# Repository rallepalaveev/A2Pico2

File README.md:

# A2Pico2

This space is decicated to A2Pico2 Project.

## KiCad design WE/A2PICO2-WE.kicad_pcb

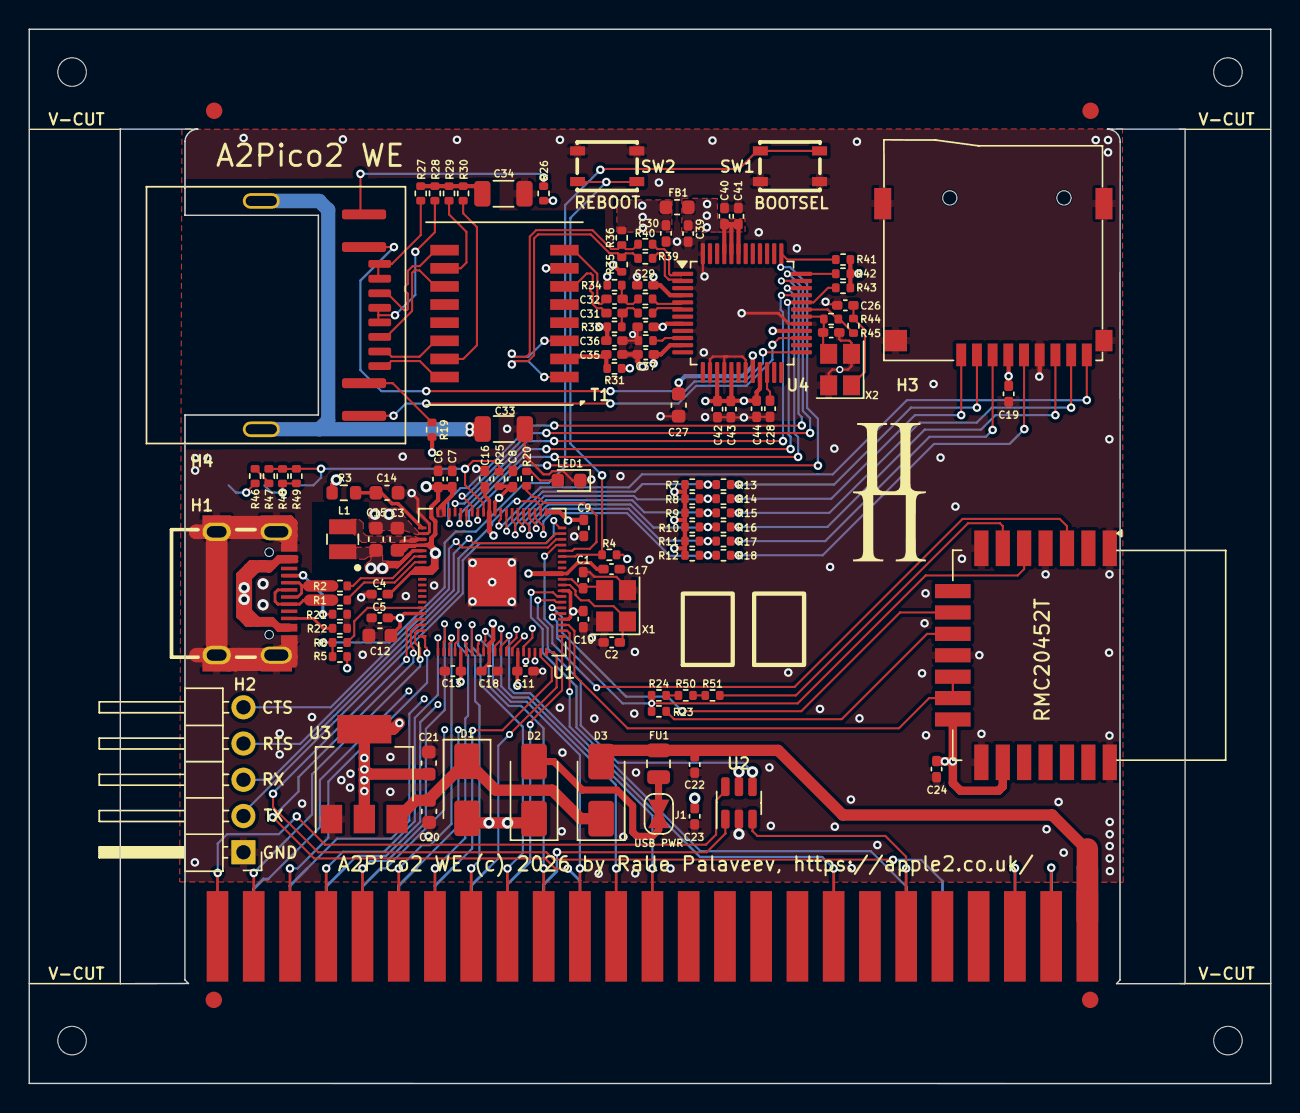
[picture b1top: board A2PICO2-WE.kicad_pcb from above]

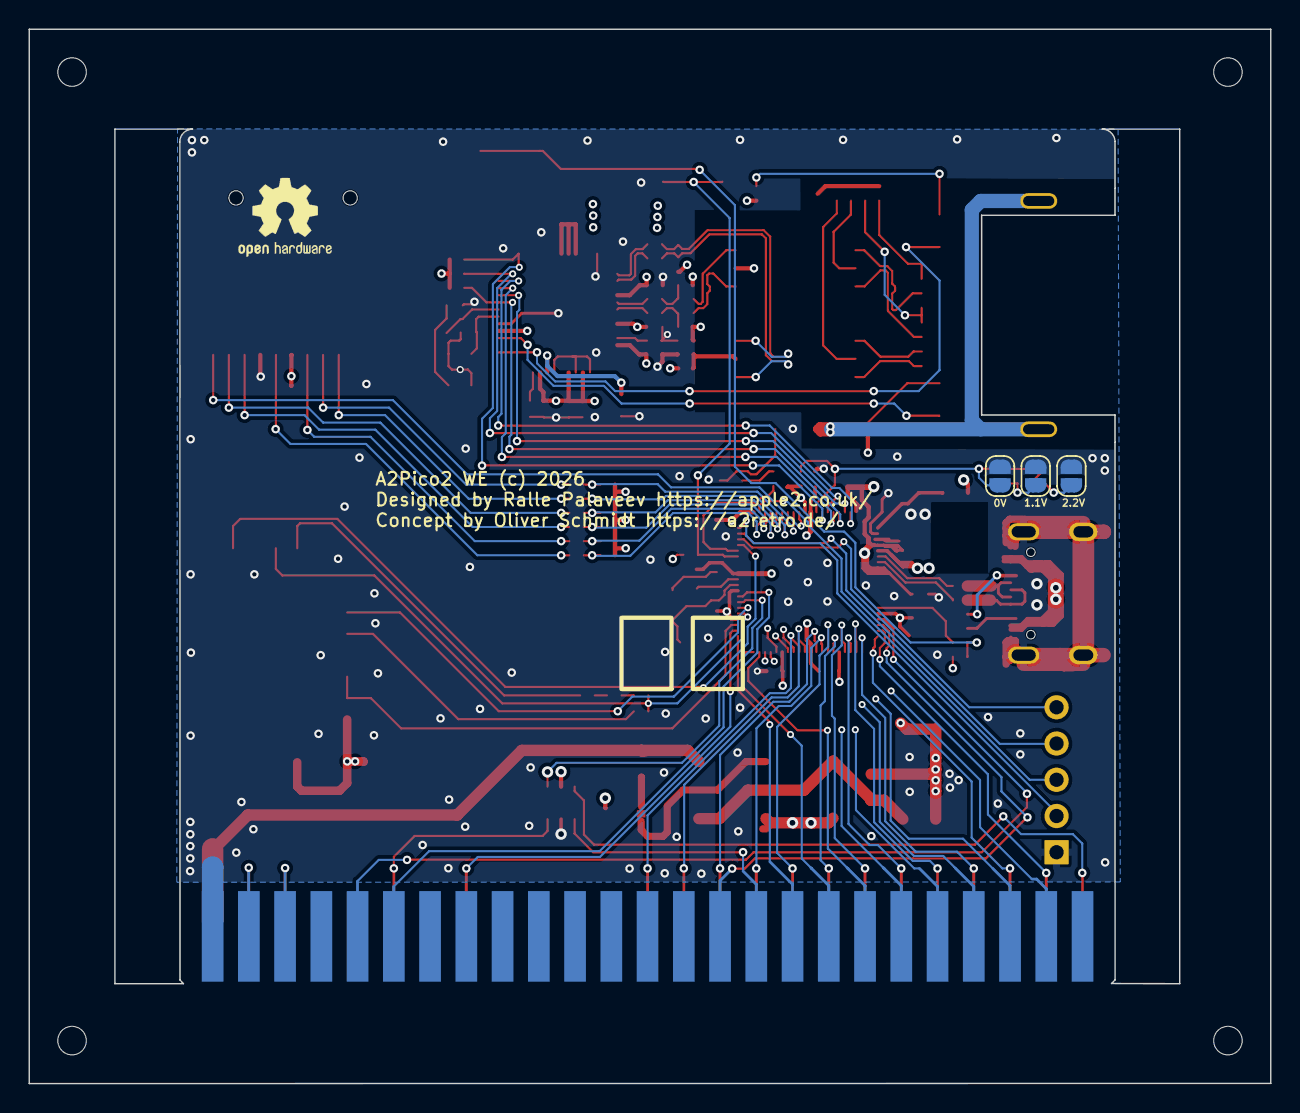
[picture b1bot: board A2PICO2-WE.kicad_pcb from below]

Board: 4 copper layers, 87.0 x 73.9 mm, 120 parts (3 on the bottom side), 90 nets.

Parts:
C1, C2, C25, C26: 18pF; C_0402_1005Metric_Pad0.74x0.62mm_HandSolder
C3, C12, C14, C27: 4.7uF; C_0603_1608Metric
C4, C5, C6, C7, C8, C9, C10, C11, C13, C16, C17, C18, C19, C22, C23, C24, C36, C37, C38, C39, C40, C41, C42, C43, C44: 100n; C_0402_1005Metric_Pad0.74x0.62mm_HandSolder
C15, C20, C21: 10uF; C_0603_1608Metric
C28: 10n; C_0402_1005Metric_Pad0.74x0.62mm_HandSolder
C29: 1u; C_0402_1005Metric_Pad0.74x0.62mm_HandSolder
C30: 1uF; C_0402_1005Metric_Pad0.74x0.62mm_HandSolder
C31, C32: 6.8n; C_0402_1005Metric_Pad0.74x0.62mm_HandSolder
C33, C34: 1nF/2kV; C_1206_3216Metric
C35: 22n; C_0402_1005Metric_Pad0.74x0.62mm_HandSolder
D1, D2, D3: SS14; D_SMA
FB1: 600Ω@100 MHz; L_0603_1608Metric
FU1: 500mA; Fuse_0805_2012Metric
H1: USB-C-16P-F(A40-00119-A52-12); USB2.0_TYPE-C(A40-00119-A52-12)
H2: PinHeader_1x05_P2.54mm_Horizontal
H3: microSD_Shou_Han; microSD_HC_Hirose_DM3AT-SF-PEJM5
H4: RJ45; RJ45_Pulse_JXD6-0001NL_Horizontal
J1: SolderJumper-2_P1.3mm_Bridged_RoundedPad1.0x1.5mm
J2, J3, J4: SolderJumper-2_P1.3mm_Open_RoundedPad1.0x1.5mm
L1: 3.3uH; L_Wuerth_MAPI-2512
LED1: LED_CHR; LED_0603_1608Metric
R1, R2: 27; R_0402_1005Metric
R3: 27; R_0603_1608Metric
R4, R6, R25, R46, R47, R48, R49: 1k; R_0402_1005Metric
R5, R7, R8, R9, R10, R11, R12, R23: 10k; R_0402_1005Metric
R13, R14, R15, R16, R17, R18, R33, R34, R35, R36: 49.9; R_0402_1005Metric
R19, R24, R26: 330; R_0402_1005Metric
R20: 1K; R_0402_1005Metric
R21, R22: 5k1; R_0402_1005Metric
R27, R28, R29, R30, R50, R51: 75; R_0402_1005Metric
R31: 10/1%; R_0402_1005Metric
R32: 12.4k/1%; R_0402_1005Metric
R37, R38, R39, R40: 3.3; R_0402_1005Metric
R41, R42, R43: 5.1k; R_0402_1005Metric
R44: 1M; R_0402_1005Metric
R45: 0; R_0402_1005Metric
RMC20452T: RMC20452T; ESP-12E
SW1, SW2: YTS-A016-X
T1: TDFN-12_2x3mm_P0.5mm
U1: RP2354B; QFN-80_EP_10x10_Pitch0.4mm
U2: SN74LVC1G11DBVR; SOT-23-6
U3: AZ1117I-H-3.3; SOT-223-3_TabPin2
U4: LQFP-48_7x7mm_P0.5mm
X1, X2: Crystal_SMD_Abracon_ABM8AIG-4Pin_3.2x2.5mm

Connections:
1V2O: C28.2, U4.22
45: H4.4, H4.5, R28.1
75: C34.1, R27.2, R28.2, R29.2, R30.2
78: H4.7, H4.8, R27.1
+1.1V: C15.1, C16.1, C17.1, C18.1, L1.1, U1.10 (DVDD), U1.32 (DVDD), U1.51 (DVDD), U1.65 (VREG_FB)
+3V3: C3.1, C4.1, C5.1, C6.1, C7.1, C8.1, C9.1, C10.1, C11.1, C12.1, C13.1, C19.1, C21.2, C23.1, C24.2, C39.2, C40.1, C41.1, FB1.1, H3.4, R3.2, R4.1, R5.2, R7.1, R8.1, R9.1, R10.1, R11.1, R12.1, R19.1, R25.1, R26.1, R41.2, R42.2, R43.2, RMC20452T.14, RMC20452T.16, U1.5 (IOVDD), U1.15 (IOVDD), U1.24 (IOVDD), U1.29 (IOVDD), U1.41 (IOVDD), U1.50 (IOVDD), U1.59 (IOVDD), U1.60 (IOVDD), U1.64 (VREG_VIN), U1.68 (IOVDD), U1.69 (IOVDD), U1.76 (IOVDD), U2.5, U3.2, U4.28, U4.43, U4.44, U4.45
+3V3a: C29.2, C30.2, C37.2, C38.2, C42.2, C43.2, C44.2, FB1.2, R31.2, R35.1, R36.2, U4.4, U4.8, U4.11, U4.15, U4.17, U4.21
+5V: C22.2, D3.2, FU1.1
+5V-1: D2.2, FU1.2, J1.1, J1.2
/BOOTSEL: R5.1, R6.1, SW1.1
/D+: R1.2, U1.67 (USB_D+)
/D-: R2.2, U1.66 (USB_D-)
/USB_D+: H1.A6, H1.B6, R1.1
/USB_D-: H1.A7, H1.B7, R2.1
/VIN: C20.1, D1.1, D3.1, U3.3
/~QSPI_CS_{0}: R6.2, U1.75 (~QSPI_CS)
A5-net: H1.A5, R21.1
ACTn: H4.11, U4.25
ACTn+: H4.12, R26.2
B5-net: H1.B5, R22.1
CLK: R12.2, R18.1, U1.43 (GPIO34)
CLK_: H3.5, R18.2
CMD: R11.2, R17.1, U1.44 (GPIO35)
CMD_: H3.3, R17.2
DAT0: R10.2, R16.1, U1.45 (GPIO36)
DAT0_: H3.7, R16.2
DAT1: R9.2, R15.1, U1.46 (GPIO37)
DAT1_: H3.8, R15.2
DAT2: R8.2, R14.1, U1.47 (GPIO38)
DAT2_: H3.1, R14.2
DAT3: R7.2, R13.1, U1.48 (GPIO39)
DAT3_: H3.2, R13.2
Detect: H3.9, U1.49 (GPIO40)
ETH_CSn: R43.1, U1.56 (GPIO45), U4.32
ETH_INTn: R42.1, U1.54 (GPIO43), U4.36
ETH_RSTn: R41.1, U1.53 (GPIO42), U4.37
ETH_Rx: U1.55 (GPIO44), U4.34
ETH_SCK: U1.57 (GPIO46), U4.33
ETH_Tx: U1.58 (GPIO47), U4.35
ExtCap: C27.2, U4.20
ExtRes: R32.2, U4.10
GND: C1.2, C2.2, C3.2, C4.2, C5.2, C6.2, C7.2, C8.2, C9.2, C10.2, C11.2, C12.2, C13.2, C14.1, C15.2, C16.2, C17.2, C18.2, C19.2, C20.2, C21.1, C22.1, C23.2, C24.1, C25.2, C26.1, C27.1, C28.1, C29.1, C30.1, C33.2, C34.2, C35.2, C36.2, C37.1, C38.1, C39.1, C40.2, C41.2, C42.1, C43.1, C44.1, H1.0, H1.A1, H1.A12, H1.B1, H1.B12, H2.1, H3.6, H3.10, J2.2, J3.2, J4.2, LED1.1 (K), R21.2, R22.2, R32.1, RMC20452T.1, RMC20452T.4, RMC20452T.7, RMC20452T.11, RMC20452T.15, RMC20452T.21, SW1.2, SW2.1, U1.62 (GND), U1.81 (GND), U2.2, U3.1, U4.3, U4.9, U4.14, U4.16, U4.19, U4.29, U4.48, X1.2, X1.4, X2.2, X2.4
HWSel: J4.1, R25.2, R47.1, R48.1, R49.1, U1.52 (GPIO41)
HWSel1.1: J3.1, R48.2, R49.2
HWSel2.2: J2.1, R46.2
HWSel3.3: R46.1, R47.2
LED: R20.1, U1.36 (GPIO28)
LINKn: H4.9, U4.27
LINKn+: H4.10, R19.2
unnamed: C14.2, R3.1, U1.61 (VREG_AVDD)
unnamed: L1.2, U1.63 (VREG_XL)
unnamed: C2.1, U1.30 (XIN), X1.1
unnamed: C1.1, U1.31 (XOUT), X1.3
RCT: C36.1, R33.1, R34.1, T1.7
RD+: C31.1, T1.6
RD-: C32.1, T1.8
RX+: H4.3, T1.11
RX-: H4.6, T1.9
RXCT: R29.1, T1.10
RXN: R38.2, U4.5
RXN_: C32.2, R34.2, R38.1
RXP: R37.2, U4.6
RXP_: C31.2, R33.2, R37.1
TCT: C35.1, R31.1, T1.2
TD+: R35.2, R39.1, T1.1
TD-: R36.1, R40.1, T1.3
TX+: H4.1, T1.16
TX-: H4.2, T1.14
TXCT: R30.1, T1.15
TXN: R40.2, U4.1
TXP: R39.2, U4.2
UART_CTS: H2.5, U1.38 (GPIO30)
UART_RTS: H2.4, U1.39 (GPIO31)
UART_Rx: H2.3, U1.42 (GPIO33)
UART_Tx: H2.2, U1.40 (GPIO32)
VBUS: D1.2, D2.1, H1.A4, H1.A9, H1.B4, H1.B9
WL_CLK: RMC20452T.3, U1.37 (GPIO29)
WL_CS: RMC20452T.9, U1.26 (GPIO25)
WL_D: R23.1, R24.1, RMC20452T.5, U1.25 (GPIO24)
WL_D_IRQ: R23.2, RMC20452T.10
WL_D_o: R51.2, RMC20452T.6
WL_D_o1: R24.2, R50.1
WL_D_o2: R50.2, R51.1
WL_ON: RMC20452T.12, RMC20452T.13, U1.23 (GPIO23)
XI: C25.1, R44.1, U4.30, X2.3
XO: R44.2, R45.1, U4.31
XO_: C26.2, R45.2, X2.1
net1: LED1.2 (A), R20.2
~ENBL: U1.27 (GPIO26), U2.4
~RP-RESET: R4.2, SW2.2, U1.35 (RUN)

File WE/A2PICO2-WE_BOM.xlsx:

Comment | Designator | Footprint | JLCPCB Part #（optional）
18pF | C1,C2,C25,C26 | 0402 | C1549
6.3V 4.7uF 0603 | C3,C12,C14,C27 | 0603 | C8032
6.3V 10uF 0603 | C15,C20,C21 | 0603 | C19702
16V 100nF 0402 | C4,C5,C6,C7,C8,C9,C10,C11,C13,C16,C17,C18,C19,C22,C23,C24,C36,C37,C38,C39,C40,C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 | 0402 | C1525
10nF | C28 | 0402 | C15195
1uF | C29,C30 | 0402 | C52923
6.8nF | C31,C32 | 0402 | C93654
1nF/2kV | C33,C34 | 1206 | C9196
22nF | C35 | 0402 | C1532
SS14 | D1,D2,D3 | SMA(DO-214AC) | C2480
6V 500mA Resettable Fuse | FU1 | 0805-50 | C269104
USB-C-16P-F | H1 |  | C2765186
1.28mm Gold Deck MicroSD card (TF card) Self bomb SMD SD Card Connectors ROHS | H3 | SMD | C393941
RJ45 | H4 |  | C708645
3.3uH | L1 |  | C48783272
BLM18PG121SN1D | FB1 |  | C14709
White LED A13150060VS75000 | LED1 | SMD,1.6x0.8mm | C397049
5k1 | R21,R22,R41,R42,R43 | 0402 | C25905
27 | R1,R2 | 0402 | C25100
10k | R5,R7,R8,R9,R10,R11,R12,R23 | 0402 | C25744
1k | R4,R6,R20,R25,R46,R47,R48,R49 | 0402 | C11702
1M | R44 | 0402 | C26083
0 | R45 | 0402 | C17168
10/1% | R31 | 0402 | C25077
12.4k/1% | R32 | 0402 | C11692
49.9 | R13,R14,R15,R16,R17,R18,R33,R34,R35,R36 | 0402 | C25120
27 | R3 | 0603 | C25190
3.3 | R37,R38,R39,R40 | 0402 | C2933094
330 | R19,R24,R26 | 0402 | C25104
75 | R27,R28,R29,R30,R50,R51 | 0402 | C25133
YTS-A016-X | SW1,SW2 |  | C2910672
RP2354B-A2 | U1 |  | C39843328
SN74LVC1G11DBVR | U2 | SOT-23-6 | C51939610
AZ1117IH-3.3TRG1 | U3 | SOT-223-4 | C108495
W5500 | U4 | LQFP-48_7x7mm_P0.5mm | C32843
B1601S | T1 | TDFN-12_2x3mm_P0.5mm | C510548
12MHz | X1 | SMD3225-4P | C403945
25MHz | X2 | SMD3225-4P | C164045

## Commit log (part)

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2026-02-08 Add MIT License to the project
2026-02-08 Update Readme.md to clarify version 1.0 obsolescence
    Clarify that version 1.0 is obsolete due to unnecessary inversion and OC driver usage.
2026-02-08 Update Readme with storage card functionality
    Expanded description to include details about the expansion mass storage card functionality.

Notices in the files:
WE/A2PICO2-WE.kicad_pcb:
A2Pico2 WE (c) 2026
A2Pico2 WE (c) 2026 by Ralle Palaveev, https://apple2.co.uk
